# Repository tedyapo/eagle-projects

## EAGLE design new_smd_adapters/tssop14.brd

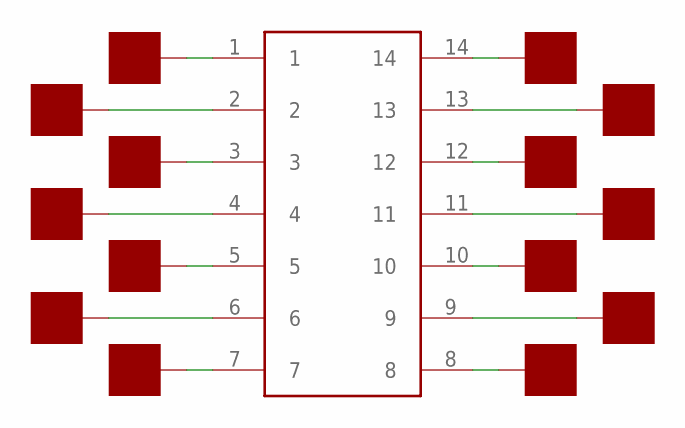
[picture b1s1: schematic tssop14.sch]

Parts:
IC1: TSSOP14
U$1, U$2, U$3, U$4, U$5, U$6, U$7, U$8, U$9, U$10, U$11, U$12, U$13, U$14: PAD50MIL; PAD_50MIL

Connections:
unnamed: IC1.1, U$8.P$1
unnamed: IC1.2, U$9.P$1
unnamed: IC1.3, U$10.P$1
unnamed: IC1.4, U$11.P$1
unnamed: IC1.5, U$12.P$1
unnamed: IC1.6, U$13.P$1
unnamed: IC1.7, U$14.P$1
unnamed: IC1.8, U$7.P$1
unnamed: IC1.9, U$6.P$1
unnamed: IC1.10, U$5.P$1
unnamed: IC1.11, U$4.P$1
unnamed: IC1.12, U$3.P$1
unnamed: IC1.13, U$2.P$1
unnamed: IC1.14, U$1.P$1

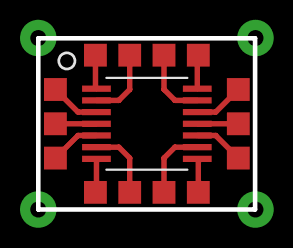
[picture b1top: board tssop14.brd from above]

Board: 2 copper layers, 12.0 x 9.5 mm, 15 parts (0 on the bottom side), 14 nets.

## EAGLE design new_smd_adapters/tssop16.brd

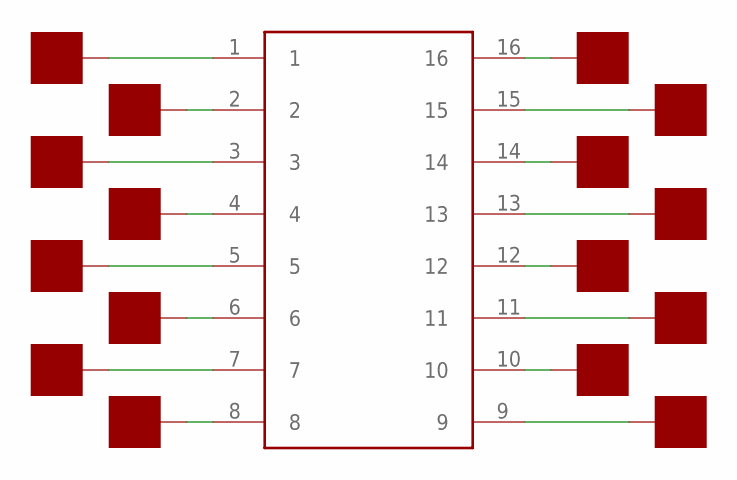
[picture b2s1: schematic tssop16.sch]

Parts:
IC1: TSSOP-16
U$1, U$2, U$3, U$4, U$5, U$6, U$7, U$8, U$9, U$10, U$11, U$12, U$13, U$14, U$15, U$16: PAD50MIL; PAD_50MIL

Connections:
unnamed: IC1.1, U$16.P$1
unnamed: IC1.2, U$15.P$1
unnamed: IC1.3, U$14.P$1
unnamed: IC1.4, U$13.P$1
unnamed: IC1.5, U$12.P$1
unnamed: IC1.6, U$11.P$1
unnamed: IC1.7, U$10.P$1
unnamed: IC1.8, U$9.P$1
unnamed: IC1.9, U$8.P$1
unnamed: IC1.10, U$7.P$1
unnamed: IC1.11, U$6.P$1
unnamed: IC1.12, U$5.P$1
unnamed: IC1.13, U$4.P$1
unnamed: IC1.14, U$3.P$1
unnamed: IC1.15, U$2.P$1
unnamed: IC1.16, U$1.P$1

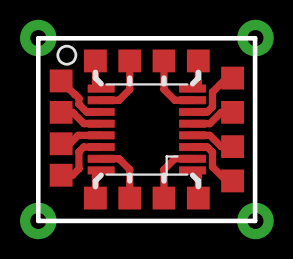
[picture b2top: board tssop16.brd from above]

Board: 2 copper layers, 12.0 x 10.1 mm, 17 parts (0 on the bottom side), 16 nets.

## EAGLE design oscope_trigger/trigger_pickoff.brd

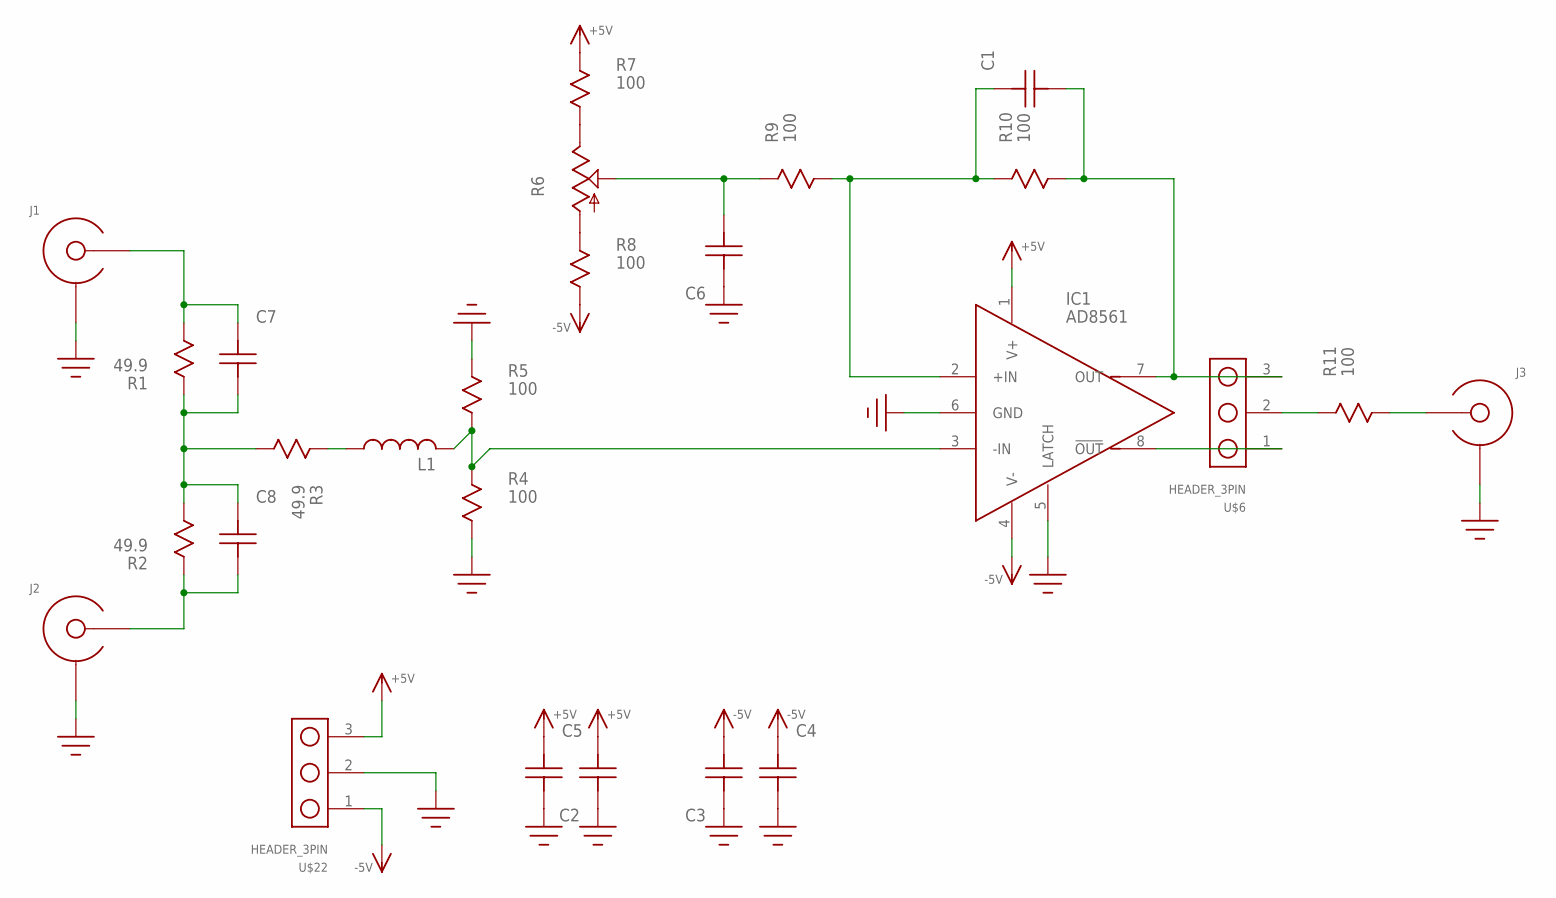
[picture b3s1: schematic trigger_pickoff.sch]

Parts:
C1, C2, C3, C6, C7, C8: C0603
C4, C5: C0805; 0805
IC1: AD8561; SOIC8
J1, J2, J3: EDGE_LAUNCH_JACK; EDGE_LAUNCH_RF_CON
L1: INDUCTOR; R0603
R1, R2, R3: 49.9; R0603
R4, R5, R7, R8, R9, R10, R11: 100; R0603
R6: TRIM_US-SP19L; SP19L
U$6, U$22: HEADER_3PIN

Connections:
+5V: C2.P$1, C5.P$2, IC1.1 (V+), R7.P$1, U$22.3
-5V: C3.P$1, C4.P$2, IC1.4 (V-), R8.P$2, U$22.1
GND: C2.P$2, C3.P$2, C4.P$1, C5.P$1, C6.P$2, IC1.5 (LATCH), IC1.6 (GND), J1.GND@1 (SHIELD), J1.GND@2 (SHIELD), J1.GND@3 (SHIELD), J1.GND@4 (SHIELD), J1.GND@5 (SHIELD), J1.GND@6 (SHIELD), J1.GND@7 (SHIELD), J1.GND@8 (SHIELD), J1.GND@9 (SHIELD), J1.GND@10 (SHIELD), J1.GND@11 (SHIELD), J1.GND@12 (SHIELD), J1.SHIELD@1 (SHIELD), J1.SHIELD@2 (SHIELD), J2.GND@1 (SHIELD), J2.GND@2 (SHIELD), J2.GND@3 (SHIELD), J2.GND@4 (SHIELD), J2.GND@5 (SHIELD), J2.GND@6 (SHIELD), J2.GND@7 (SHIELD), J2.GND@8 (SHIELD), J2.GND@9 (SHIELD), J2.GND@10 (SHIELD), J2.GND@11 (SHIELD), J2.GND@12 (SHIELD), J2.SHIELD@1 (SHIELD), J2.SHIELD@2 (SHIELD), J3.GND@1 (SHIELD), J3.GND@2 (SHIELD), J3.GND@3 (SHIELD), J3.GND@4 (SHIELD), J3.GND@5 (SHIELD), J3.GND@6 (SHIELD), J3.GND@7 (SHIELD), J3.GND@8 (SHIELD), J3.GND@9 (SHIELD), J3.GND@10 (SHIELD), J3.GND@11 (SHIELD), J3.GND@12 (SHIELD), J3.SHIELD@1 (SHIELD), J3.SHIELD@2 (SHIELD), R4.P$2, R5.P$1, U$22.2
unnamed: C7.P$2, J1.CENTER, R1.P$2
unnamed: C7.P$1, C8.P$2, R1.P$1, R2.P$2, R3.P$2
unnamed: C8.P$1, J2.CENTER, R2.P$1
unnamed: IC1.3 (-IN), L1.P$2 (2), R4.P$1, R5.P$2
unnamed: R11.P$1, U$6.2
unnamed: C1.P$1, IC1.7 (OUT), R10.P$2, U$6.3
unnamed: IC1.8 (!OUT!), U$6.1
unnamed: R6.E, R7.P$2
unnamed: R6.A, R8.P$1
unnamed: C6.P$1, R6.S, R9.P$1
unnamed: C1.P$2, IC1.2 (+IN), R9.P$2, R10.P$1
unnamed: J3.CENTER, R11.P$2
unnamed: L1.P$1 (1), R3.P$1

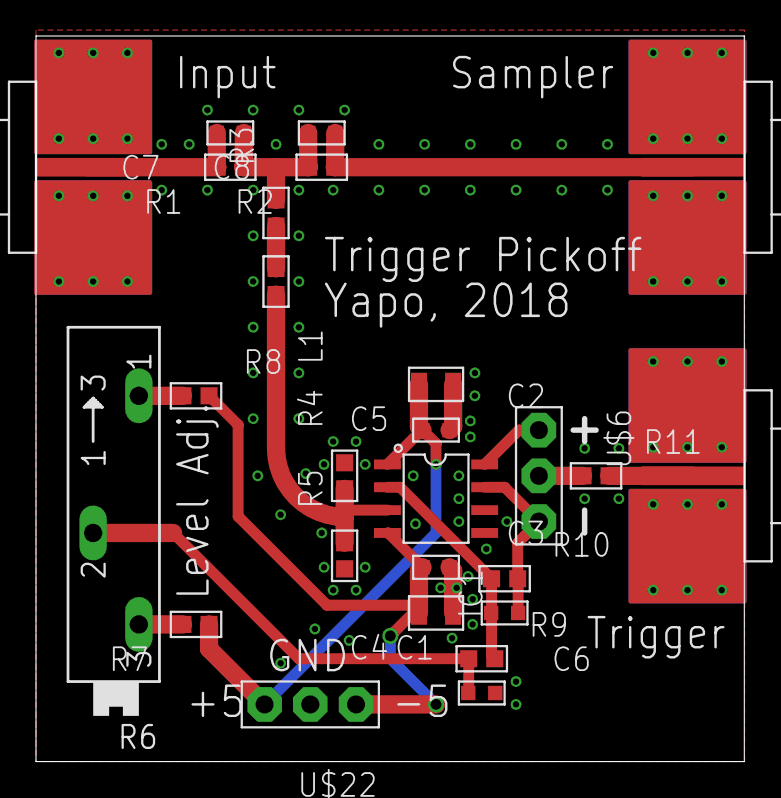
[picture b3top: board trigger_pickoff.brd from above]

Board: 2 copper layers, 39.4 x 40.3 mm, 26 parts (0 on the bottom side), 16 nets.

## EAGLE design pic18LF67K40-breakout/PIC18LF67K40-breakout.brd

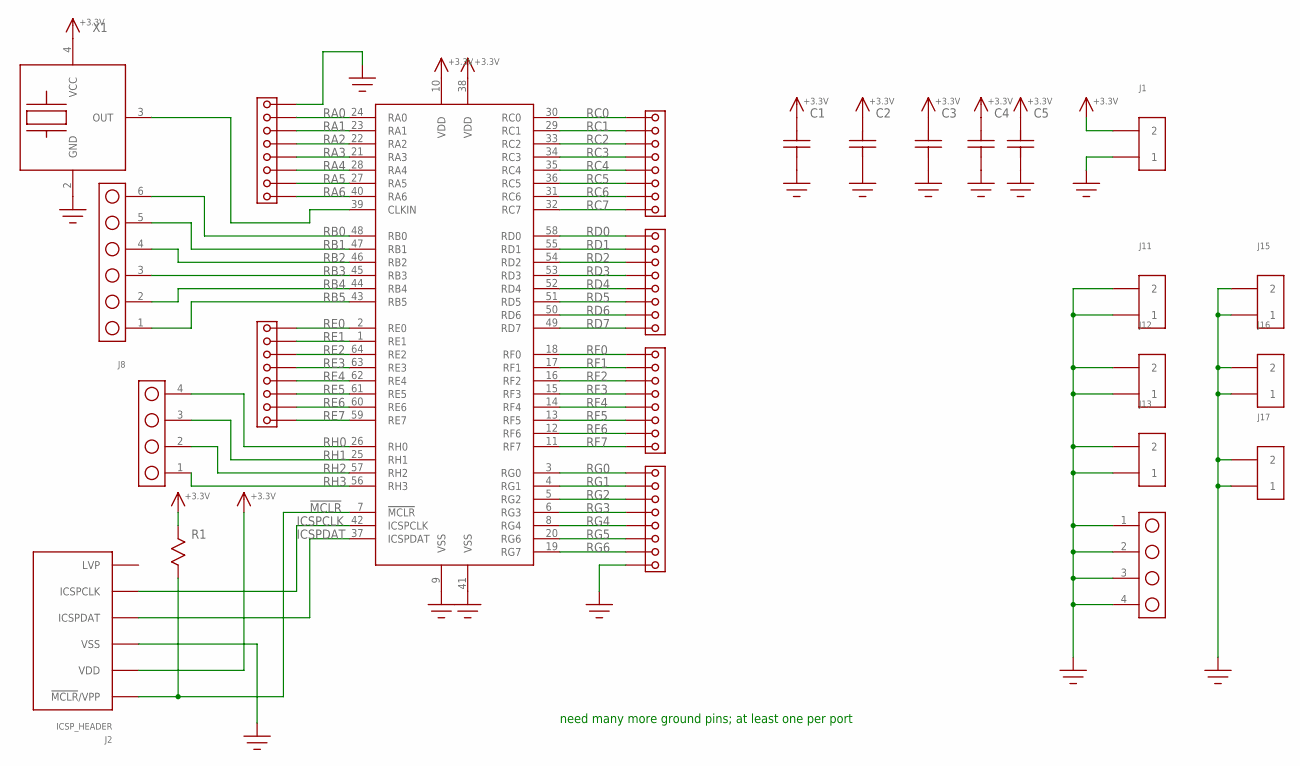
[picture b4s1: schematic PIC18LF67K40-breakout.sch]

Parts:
C1, C2: C1206; 1206
C3, C4, C5: C0603
IC1: PIC18LF67K40; TQFP-100-10X10
J1, J11, J12, J13, J15, J16, J17: HEADER_2PIN
J2: ICSP_HEADER; HEADER_6PIN
J3, J4, J5, J6, J7, J10: HEADER_8PIN_TIGHT; HEADER_8_PIN
J8: HEADER_6PIN
J9, J14: HEADER_4PIN
R1: R0603
X1: XTAL_OSC; XTAL_3.2X5

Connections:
!MCLR!: IC1.7 (!MCLR!), J2.1 (!MCLR!/VPP), R1.P$2
+3.3V: C1.P$2, C2.P$2, C3.P$2, C4.P$2, C5.P$2, IC1.10 (VDD), IC1.38 (VDD), J1.2, J2.2 (VDD), R1.P$1, X1.4 (VCC)
GND: C1.P$1, C2.P$1, C3.P$1, C4.P$1, C5.P$1, IC1.9 (VSS), IC1.41 (VSS), J1.1, J2.3 (VSS), J6.8, J10.8, J11.1, J11.2, J12.1, J12.2, J13.1, J13.2, J14.1, J14.2, J14.3, J14.4, J15.1, J15.2, J16.1, J16.2, J17.1, J17.2, X1.2 (GND)
ICSPCLK: IC1.42 (ICSPCLK), J2.5 (ICSPCLK)
ICSPDAT: IC1.37 (ICSPDAT), J2.4 (ICSPDAT)
unnamed: IC1.39 (CLKIN), X1.3 (OUT)
RA0: IC1.24 (RA0), J6.7
RA1: IC1.23 (RA1), J6.6
RA2: IC1.22 (RA2), J6.5
RA3: IC1.21 (RA3), J6.4
RA4: IC1.28 (RA4), J6.3
RA5: IC1.27 (RA5), J6.2
RA6: IC1.40 (RA6), J6.1
RB0: IC1.48 (RB0), J8.6
RB1: IC1.47 (RB1), J8.5
RB2: IC1.46 (RB2), J8.4
RB3: IC1.45 (RB3), J8.3
RB4: IC1.44 (RB4), J8.2
RB5: IC1.43 (RB5), J8.1
RC0: IC1.30 (RC0), J3.1
RC1: IC1.29 (RC1), J3.2
RC2: IC1.33 (RC2), J3.3
RC3: IC1.34 (RC3), J3.4
RC4: IC1.35 (RC4), J3.5
RC5: IC1.36 (RC5), J3.6
RC6: IC1.31 (RC6), J3.7
RC7: IC1.32 (RC7), J3.8
RD0: IC1.58 (RD0), J4.1
RD1: IC1.55 (RD1), J4.2
RD2: IC1.54 (RD2), J4.3
RD3: IC1.53 (RD3), J4.4
RD4: IC1.52 (RD4), J4.5
RD5: IC1.51 (RD5), J4.6
RD6: IC1.50 (RD6), J4.7
RD7: IC1.49 (RD7), J4.8
RE0: IC1.2 (RE0), J7.8
RE1: IC1.1 (RE1), J7.7
RE2: IC1.64 (RE2), J7.6
RE3: IC1.63 (RE3), J7.5
RE4: IC1.62 (RE4), J7.4
RE5: IC1.61 (RE5), J7.3
RE6: IC1.60 (RE6), J7.2
RE7: IC1.59 (RE7), J7.1
RF0: IC1.18 (RF0), J5.1
RF1: IC1.17 (RF1), J5.2
RF2: IC1.16 (RF2), J5.3
RF3: IC1.15 (RF3), J5.4
RF4: IC1.14 (RF4), J5.5
RF5: IC1.13 (RF5), J5.6
RF6: IC1.12 (RF6), J5.7
RF7: IC1.11 (RF7), J5.8
RG0: IC1.3 (RG0), J10.1
RG1: IC1.4 (RG1), J10.2
RG2: IC1.5 (RG2), J10.3
RG3: IC1.6 (RG3), J10.4
RG4: IC1.8 (RG4), J10.5
RG5: IC1.20 (RG6), J10.6
RG6: IC1.19 (RG7), J10.7
RH0: IC1.26 (RH0), J9.4
RH1: IC1.25 (RH1), J9.3
RH2: IC1.57 (RH2), J9.2
RH3: IC1.56 (RH3), J9.1

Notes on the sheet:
need many more ground pins; at least one per port

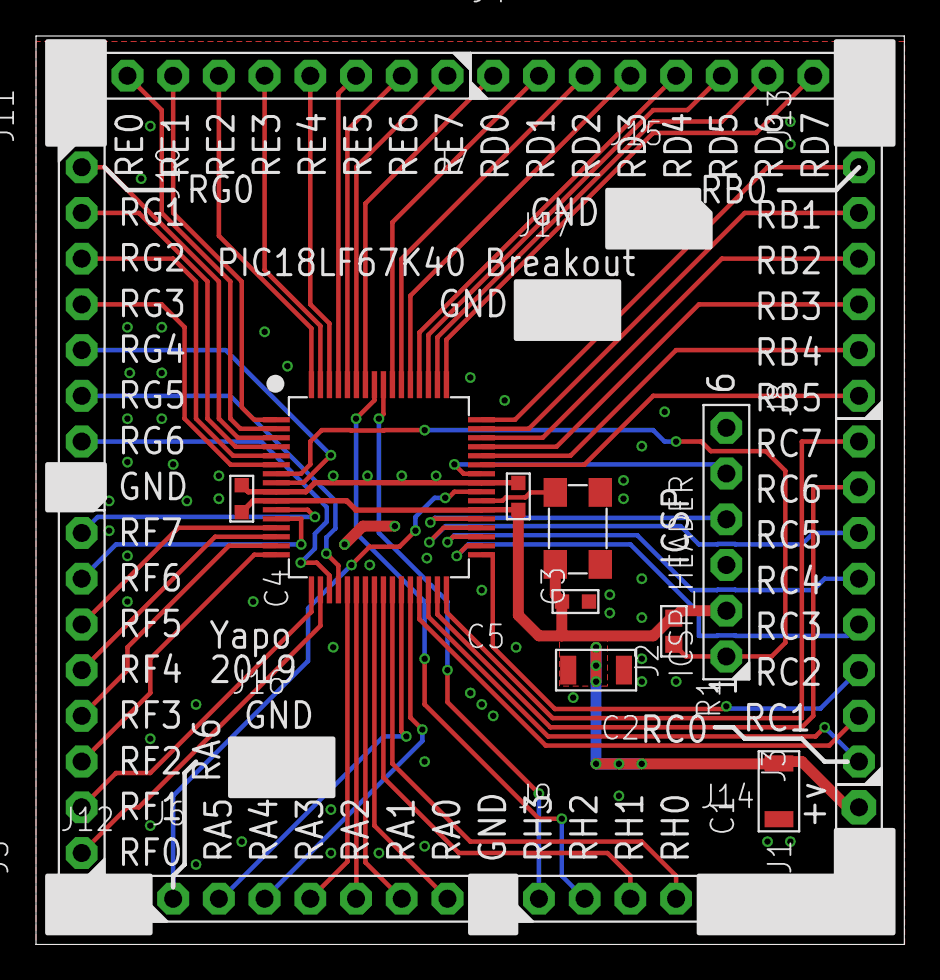
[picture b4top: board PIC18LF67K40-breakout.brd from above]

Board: 2 copper layers, 48.2 x 50.5 mm, 25 parts (0 on the bottom side), 62 nets.

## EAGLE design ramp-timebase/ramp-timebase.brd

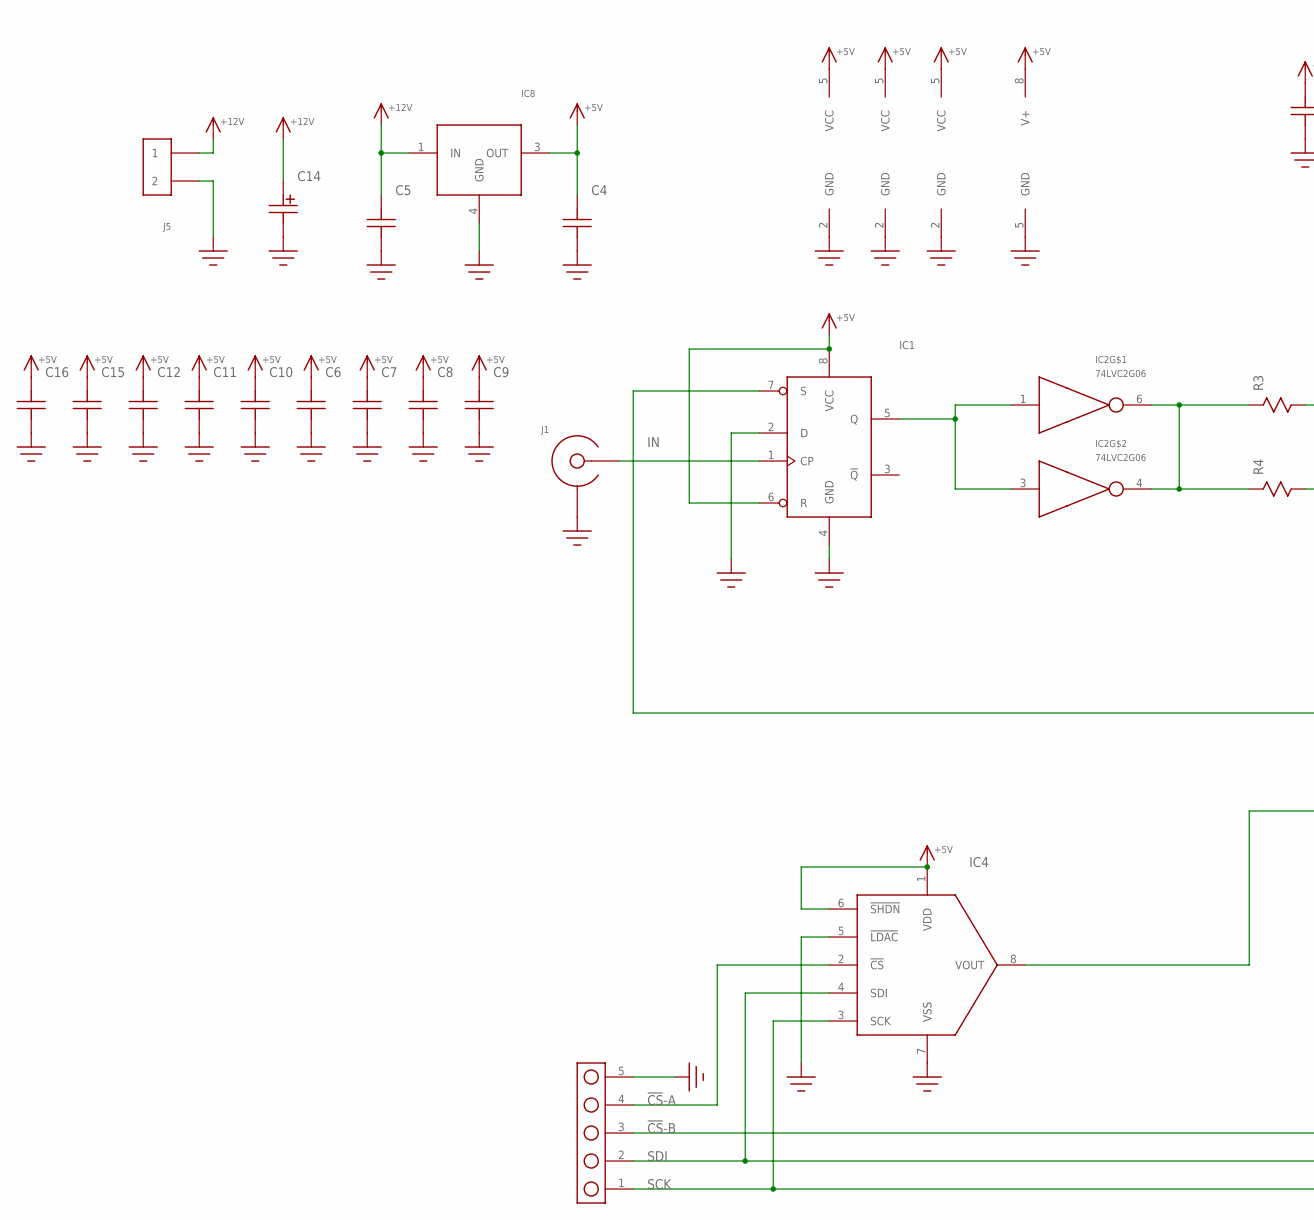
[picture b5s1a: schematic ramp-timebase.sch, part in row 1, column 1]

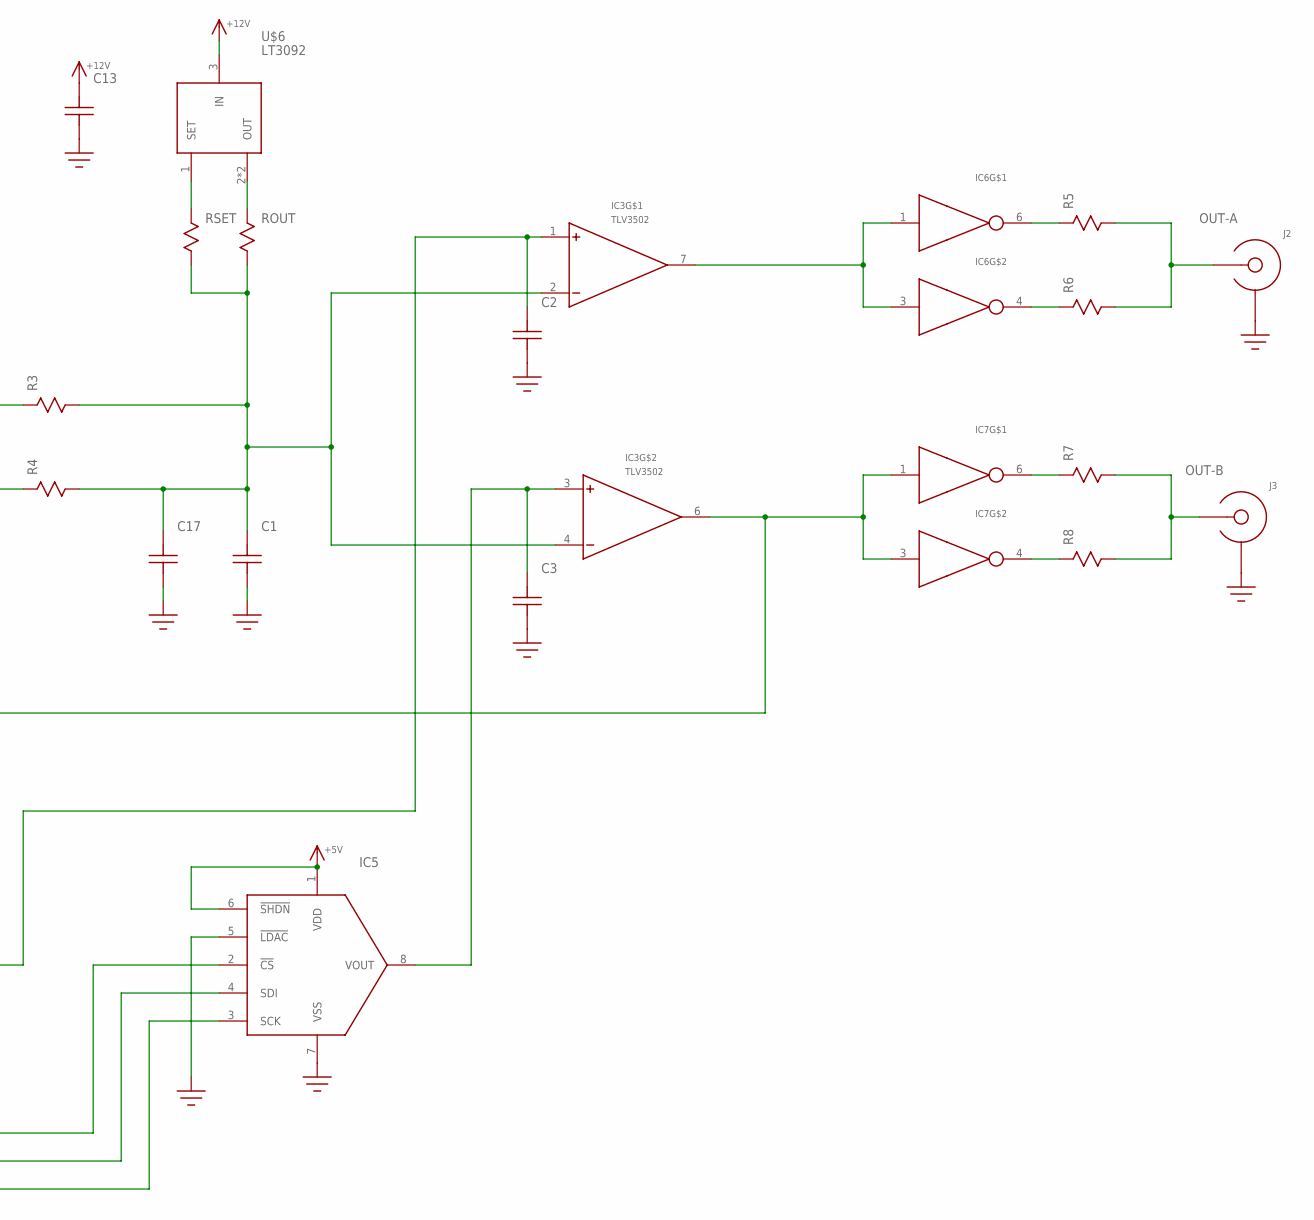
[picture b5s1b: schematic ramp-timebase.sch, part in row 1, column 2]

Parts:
C1, C2, C3, C6, C7, C8, C9, C10, C11, C12, C13, C15, C16: C0603
C4, C5, C17: C1206; 1206
C14: C-POLARIZED; CAP-E61
IC1: 74LVC2G74; SSOP8
IC2: 74LVC2G06; SOT23-6
IC3: TLV3502; SOIC8
IC4, IC5: MCP48X1; SOIC8
IC6, IC7: 74LVC2G04; SOT23-6
IC8: MC78M00; DPAK
J1, J2, J3: SMA-EDGE-LAUNCH4020_TAPER; SMA_EDGE_LAUNCH_2L_4020_TAPER
J4: HEADER_5PIN
J5: HEADER_2PINSCREW-TERM; FCI_20020316_SCREW_TERM_2P
R3, R4: R0805
R5, R6, R7, R8: R1206
ROUT: R0805
RSET: R0805
U$6: LT3092; SOT-223

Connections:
!CS!-A: IC4.2 (!CS!), J4.4
!CS!-B: IC5.2 (!CS!), J4.3
+5V: C4.P$2, C6.P$2, C7.P$2, C8.P$2, C9.P$2, C10.P$2, C11.P$2, C12.P$2, C15.P$2, C16.P$2, IC1.6 (R), IC1.8 (VCC), IC2.5 (VCC), IC3.8 (V+), IC4.1 (VDD), IC4.6 (!SHDN!), IC5.1 (VDD), IC5.6 (!SHDN!), IC6.5 (VCC), IC7.5 (VCC), IC8.3 (OUT)
+12V: C5.P$2, C13.P$2, C14.+, IC8.1 (IN), J5.P$1 (1), U$6.3 (IN)
GND: C1.P$1, C2.P$1, C3.P$1, C4.P$1, C5.P$1, C6.P$1, C7.P$1, C8.P$1, C9.P$1, C10.P$1, C11.P$1, C12.P$1, C13.P$1, C14.-, C15.P$1, C16.P$1, C17.P$1, IC1.2 (D), IC1.4 (GND), IC2.2 (GND), IC3.5 (GND), IC4.5 (!LDAC!), IC4.7 (VSS), IC5.5 (!LDAC!), IC5.7 (VSS), IC6.2 (GND), IC7.2 (GND), IC8.4 (GND), J1.BOTTOM_GND (SHIELD), J1.GND@1 (SHIELD), J1.GND@2 (SHIELD), J1.GND@3 (SHIELD), J1.GND@4 (SHIELD), J1.GND@5 (SHIELD), J1.GND@6 (SHIELD), J1.GND@7 (SHIELD), J1.GND@8 (SHIELD), J1.GND@14 (SHIELD), J1.GND@15 (SHIELD), J1.GND@16 (SHIELD), J1.GND@17 (SHIELD), J1.GND_PAD1 (SHIELD), J1.GND_PAD2 (SHIELD), J1.P$1 (SHIELD), J1.P$2 (SHIELD), J2.BOTTOM_GND (SHIELD), J2.GND@1 (SHIELD), J2.GND@2 (SHIELD), J2.GND@3 (SHIELD), J2.GND@4 (SHIELD), J2.GND@5 (SHIELD), J2.GND@6 (SHIELD), J2.GND@7 (SHIELD), J2.GND@8 (SHIELD), J2.GND@14 (SHIELD), J2.GND@15 (SHIELD), J2.GND@16 (SHIELD), J2.GND@17 (SHIELD), J2.GND_PAD1 (SHIELD), J2.GND_PAD2 (SHIELD), J2.P$1 (SHIELD), J2.P$2 (SHIELD), J3.BOTTOM_GND (SHIELD), J3.GND@1 (SHIELD), J3.GND@2 (SHIELD), J3.GND@3 (SHIELD), J3.GND@4 (SHIELD), J3.GND@5 (SHIELD), J3.GND@6 (SHIELD), J3.GND@7 (SHIELD), J3.GND@8 (SHIELD), J3.GND@14 (SHIELD), J3.GND@15 (SHIELD), J3.GND@16 (SHIELD), J3.GND@17 (SHIELD), J3.GND_PAD1 (SHIELD), J3.GND_PAD2 (SHIELD), J3.P$1 (SHIELD), J3.P$2 (SHIELD), J4.5, J5.P$2 (2)
IN: IC1.1 (CP), J1.CENTER@1 (CENTER)
unnamed: IC1.7 (S), IC3.6 (OUT), IC7.1 (IN), IC7.3 (IN)
unnamed: RSET.P$1, U$6.1 (SET)
unnamed: ROUT.P$1, U$6.2 (OUT), U$6.4 (OUT)
unnamed: C2.P$2, IC3.1 (+), IC4.8 (VOUT)
unnamed: IC1.5 (Q), IC2.1 (IN), IC2.3 (IN)
unnamed: IC2.4 (OUT), IC2.6 (OUT), R3.P$1, R4.P$1
unnamed: C3.P$2, IC3.3 (+), IC5.8 (VOUT)
unnamed: IC3.7 (OUT), IC6.1 (IN), IC6.3 (IN)
unnamed: IC7.4 (OUT), R8.P$1
unnamed: IC7.6 (OUT), R7.P$1
unnamed: IC6.4 (OUT), R6.P$1
unnamed: IC6.6 (OUT), R5.P$1
unnamed: C1.P$2, C17.P$2, IC3.2 (-), IC3.4 (-), R3.P$2, R4.P$2, ROUT.P$2, RSET.P$2
OUT-A: J2.CENTER@1 (CENTER), R5.P$2, R6.P$2
OUT-B: J3.CENTER@1 (CENTER), R7.P$2, R8.P$2
SCK: IC4.3 (SCK), IC5.3 (SCK), J4.1
SDI: IC4.4 (SDI), IC5.4 (SDI), J4.2

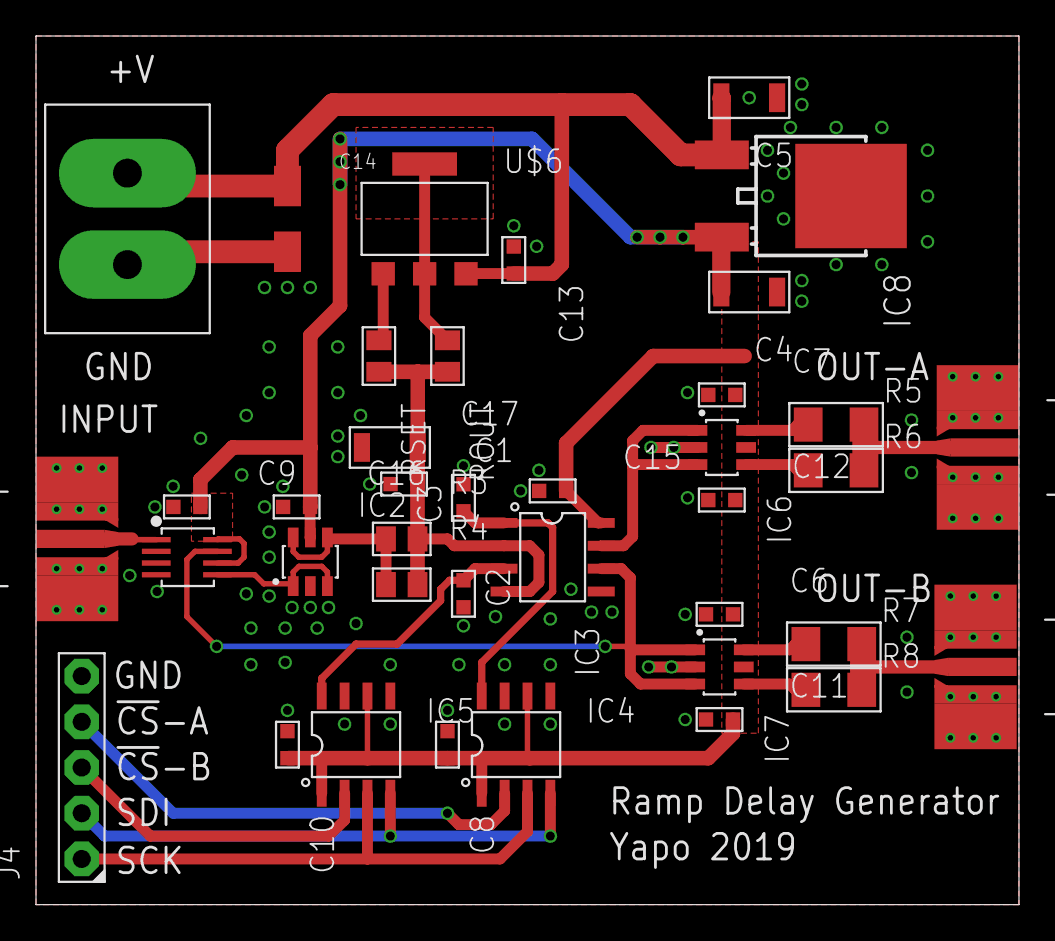
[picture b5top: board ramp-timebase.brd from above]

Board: 2 copper layers, 54.6 x 48.3 mm, 39 parts (0 on the bottom side), 23 nets.

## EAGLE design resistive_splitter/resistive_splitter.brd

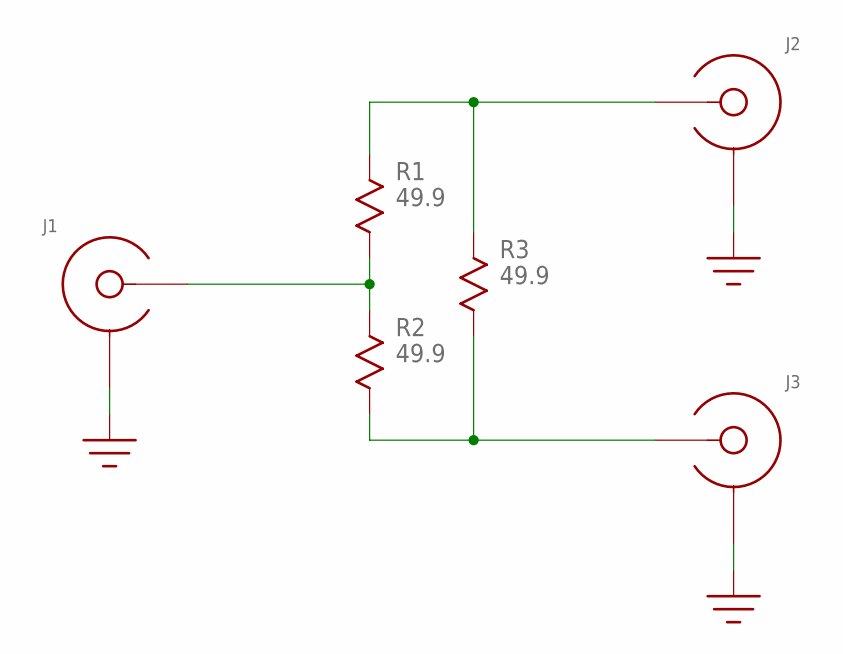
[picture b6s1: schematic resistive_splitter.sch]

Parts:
J1, J2, J3: EDGE_LAUNCH_JACKNARROW; EDGE_LAUNCH_RF_CON_NARROW
R1, R2, R3: 49.9; R0603

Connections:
GND: J1.GND@1 (SHIELD), J1.GND@2 (SHIELD), J1.GND@3 (SHIELD), J1.GND@4 (SHIELD), J1.GND@5 (SHIELD), J1.GND@6 (SHIELD), J1.SHIELD@1 (SHIELD), J1.SHIELD@2 (SHIELD), J2.GND@1 (SHIELD), J2.GND@2 (SHIELD), J2.GND@3 (SHIELD), J2.GND@4 (SHIELD), J2.GND@5 (SHIELD), J2.GND@6 (SHIELD), J2.SHIELD@1 (SHIELD), J2.SHIELD@2 (SHIELD), J3.GND@1 (SHIELD), J3.GND@2 (SHIELD), J3.GND@3 (SHIELD), J3.GND@4 (SHIELD), J3.GND@5 (SHIELD), J3.GND@6 (SHIELD), J3.SHIELD@1 (SHIELD), J3.SHIELD@2 (SHIELD)
unnamed: J1.CENTER, R1.P$2, R2.P$1
unnamed: J2.CENTER, R1.P$1, R3.P$1
unnamed: J3.CENTER, R2.P$2, R3.P$2

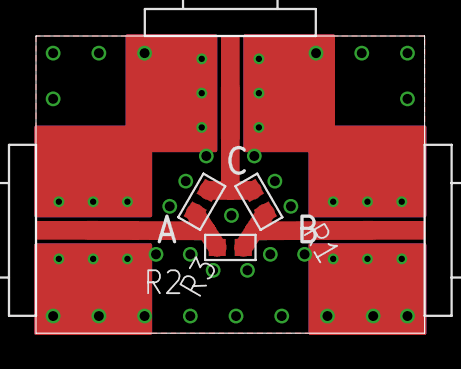
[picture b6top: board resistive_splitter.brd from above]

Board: 2 copper layers, 21.6 x 16.5 mm, 6 parts (0 on the bottom side), 4 nets.

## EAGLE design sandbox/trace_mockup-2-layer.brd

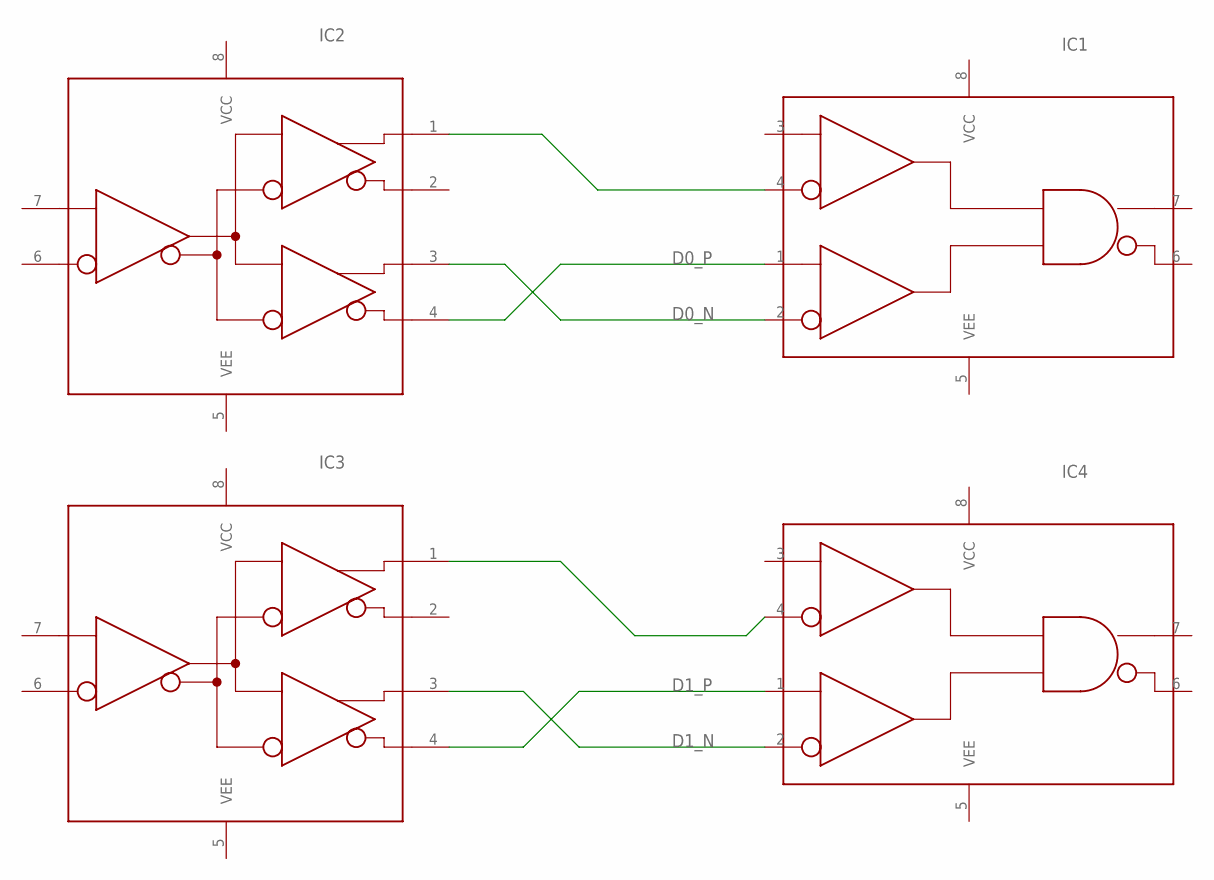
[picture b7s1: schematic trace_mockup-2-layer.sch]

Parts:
IC1, IC4: SY10EP05V; SOIC8
IC2, IC3: SY10EP11U; SOIC8

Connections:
D0_N: IC1.2 (!D0!), IC2.3 (Q1)
D0_P: IC1.1 (D0), IC2.4 (!Q1!)
D1_N: IC3.3 (Q1), IC4.2 (!D0!)
D1_P: IC3.4 (!Q1!), IC4.1 (D0)
unnamed: IC1.4 (!D1!), IC2.1 (Q0)
unnamed: IC3.1 (Q0), IC4.4 (!D1!)

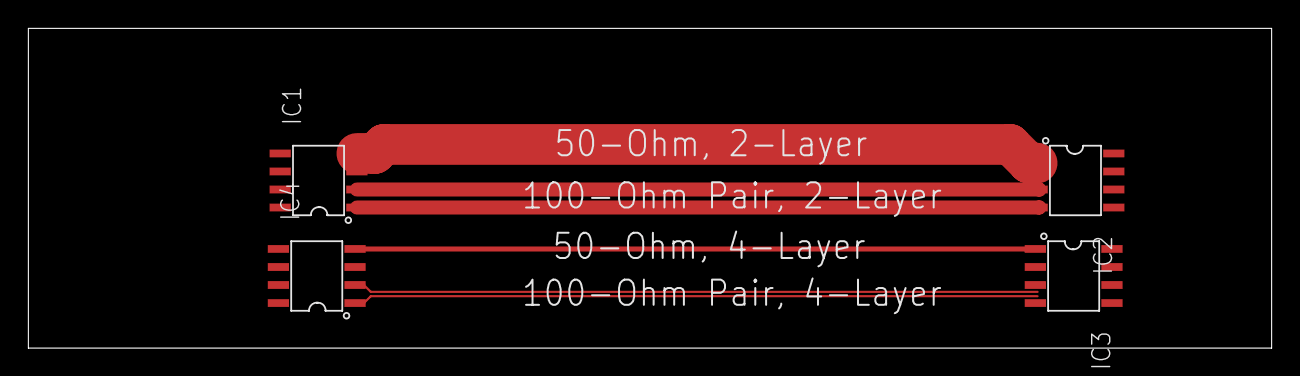
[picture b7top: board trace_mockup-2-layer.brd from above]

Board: 2 copper layers, 87.6 x 22.5 mm, 4 parts (0 on the bottom side), 6 nets.
